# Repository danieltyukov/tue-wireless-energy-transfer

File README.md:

# Wireless Energy Transfer (5XWF0)

Challenge-based learning project for the 5XWF0 Wireless Energy Transfer course at TU
Eindhoven, Q4 2024, built by a team of nine. The goal was to wirelessly power a desktop PC
from a sustainable energy source across an air gap of 10 to 20 cm, delivering at least
100 W and tracking the maximum power point. The full chain is a generator (energy source),
a DC/DC boost converter that stabilizes the variable input to 50 V, a full-bridge DC/AC
inverter, a pair of resonant magnetically coupled coils, an AC/DC rectifier, and the load,
all coordinated by a microcontroller that measures voltages and currents and sets the PWM
duty cycle and switching frequency.

My part of the project was the DC/DC boost converter: the topology and component choices,
a MATLAB script for selecting the inductor and capacitor values, the KiCad PCB, and the
hardware testing. The sections and appendices for that subsystem in the final report are
mine (design choices, testing, and the component-selection script).

## The DC/DC boost converter

The converter takes the generator's variable rectified DC (up to 30 V, limited to 10 A)
and boosts it to a regulated 50 V for the rest of the chain. Design decisions and their
reasoning:

- **Topology.** A standard boost converter, chosen over buck-boost and Cuk alternatives.
  Those give a wider input range but add an inverted output, a negative gate-drive supply,
  or a second inductor, all of which raise complexity and losses.
- **Passives.** A 75 to 125 uH inductor sized to keep the converter in continuous
  conduction mode with margin, and a 220 uF output capacitor. In simulation this holds the
  output at about 49 V with 4.95 % ripple, inside the 5 % requirement. The minimum values
  were computed with a MATLAB script that sweeps the input voltage range (`Appendix D` of
  the report).
- **Switches and diode.** An IRF640 power MOSFET, picked over the IRF630 because its lower
  on-resistance cuts conduction losses more than the added switching loss costs, and an
  MBR10100+ Schottky diode rated for the worst-case current at low duty cycle.
- **Switching frequency.** 20 kHz, a tradeoff that keeps switching losses low while still
  meeting the ripple targets without an oversized inductor.
- **Control.** A low-side gate driver so the microcontroller can drive the duty cycle
  directly, with the duty cycle held near 0.5 and constrained to keep the input current
  under the 10 A generator limit.

The board was laid out in KiCad with a continuous ground plane, current-scaled trace
widths, and component placement chosen to spread heat and limit EMI.

Testing started at low voltage and current on the PCB, cross-checked against the
breadboard build to isolate faults (a diode footprint mismatch, misplaced input
capacitors, and wrong voltage-divider resistor values were found and fixed), then ramped
up to 150 W.

## Result

The integrated system reached a tested peak efficiency of 77.36 % at 180.80 W output,
passing the 100 W minimum. The power electronics PCBs worked as designed. MPPT and
automatic load detection were designed but not fully brought up in hardware within the
project time, and the report documents the gap between the MATLAB and Simulink models and
the measured system as the main lesson for future work.

## Repository structure

```
5XWF0_Final_Report.pdf      full team report (design, models, testing, results)
dc-to-dc-maker/             DC/DC boost converter: KiCad project, gerbers, part libraries
dc-to-ac-maker/             DC/AC full-bridge inverter KiCad project
CODING/                     microcontroller firmware (STM32 F303K8 and ESP32), PWM/ADC/MPPT
STM32 - F303K8 code/        packaged STM32CubeIDE firmware builds
team-microcontroller/       microcontroller subteam working files
*.slx                       Simulink models of the full system
```

## Building and running

The converter and inverter boards open in KiCad (`.kicad_pro` / `.kicad_pcb` /
`.kicad_sch`), with gerbers included for fabrication. The firmware under
`CODING/Final Codes/C-Code` is STM32CubeIDE C for the Nucleo F303K8 (PWM plus ADC
variants, including an MPPT-via-ADC version). The `.slx` files are Simulink models of the
full transfer chain and are opened in MATLAB/Simulink.

## Technologies

KiCad (PCB design and gerbers), power electronics (boost converter, full-bridge inverter,
resonant inductive coupling), MATLAB and Simulink, STM32 (Nucleo F303K8, STM32CubeIDE, C)
and ESP32 firmware, and bench testing with an oscilloscope and impedance analyzer.

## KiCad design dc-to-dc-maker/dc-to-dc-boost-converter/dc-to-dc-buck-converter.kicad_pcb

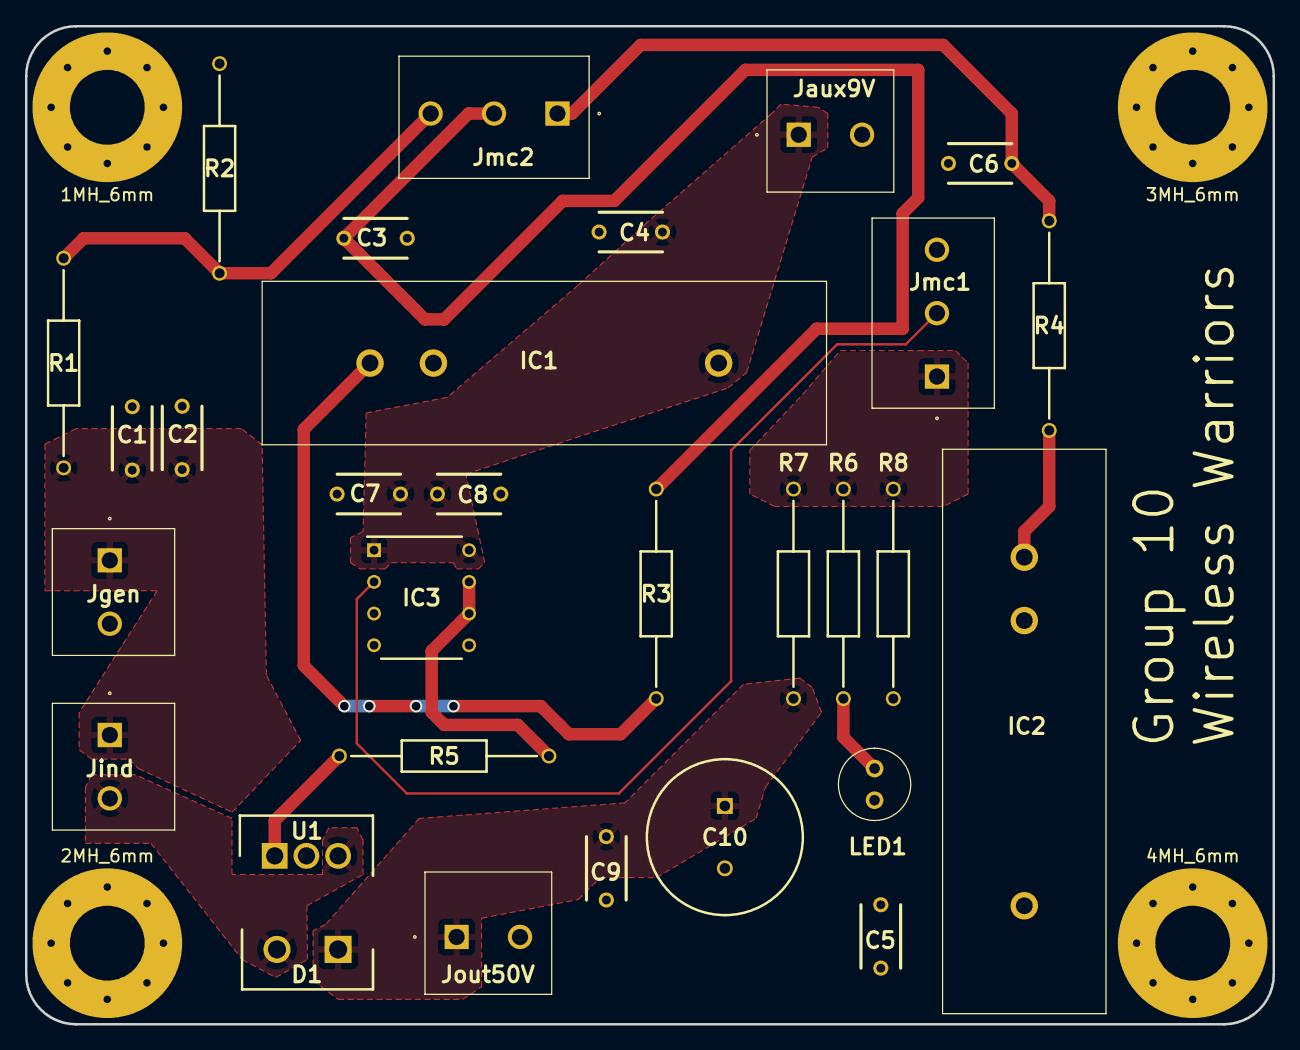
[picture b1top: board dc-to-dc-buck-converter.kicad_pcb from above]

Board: 2 copper layers, 100.0 x 80.0 mm, 34 parts (0 on the bottom side), 15 nets.

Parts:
1MH_6mm, 2MH_6mm, 3MH_6mm, 4MH_6mm: MH_6mm; MountingHole_6mm_Pad_Via
C1, C2, C3, C4, C5, C6, C7, C8, C9: 0.1uF; C322
C10: 220uF; CAPPRD500W65D1250H2200
D1: MBR10100+; TO490P480X1000X2110-2P
IC1, IC2: LA_55-P; LA55-P
IC3: EL7104CNZ; DIP762W51P254L952H533Q8N
Jaux9V: Jaux; 1715721
Jgen: Jgen; 1715721
Jind: Jind; 1715721
Jmc1, Jmc2: 1715734
Jout50V: Jout +50V; 1715721
LED1: TLUR5400
R1, R7: 20K; RESAD1680W59L680D250
R2, R8: 1K; RESAD1680W59L680D250
R3, R4: 100; RESAD1680W59L680D250
R5, R6: 10; RESAD1680W59L680D250
U1: IRF640NPBF; TO254P483X1016X1994-3P

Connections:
GND: C1.1, C2.1, C3.2, C4.2, C5.2, C6.2, C7.1, C8.1, C9.1, C10.2 (-), IC1.2 (NEG), IC2.2 (NEG), IC3.4 (GND_1), IC3.5 (GND_2), Jaux9V.2, Jgen.2, Jmc1.3, Jout50V.2, LED1.2 (K), R2.1, R8.1, U1.2 (SOURCE)
unnamed: C1.2, C2.2, Jgen.1, Jind.1, R1.2
unnamed: C3.1, Jmc2.2, R3.1
unnamed: C6.1, Jmc2.1, R4.1
unnamed: C9.2, C10.1 (+), D1.1 (K), Jout50V.1, R7.2
unnamed: D1.2 (A), Jind.2, U1.3 (DRAIN)
unnamed: IC1.1 (M), R3.2
unnamed: C4.1, C5.1, C7.2, C8.2, IC1.3 (POS), IC2.3 (POS), IC3.1 (V+_1), IC3.8 (V+_2), Jaux9V.1
unnamed: IC2.1 (M), R4.2
unnamed: IC3.2 (IN), Jmc1.2
unnamed: IC3.6 (N_OUT), IC3.7 (P_OUT), R5.1
unnamed: Jmc1.1, R6.1, R7.1, R8.2
unnamed: Jmc2.3, R1.1, R2.2
unnamed: LED1.1 (A), R6.2
unnamed: R5.2, U1.1 (GATE)

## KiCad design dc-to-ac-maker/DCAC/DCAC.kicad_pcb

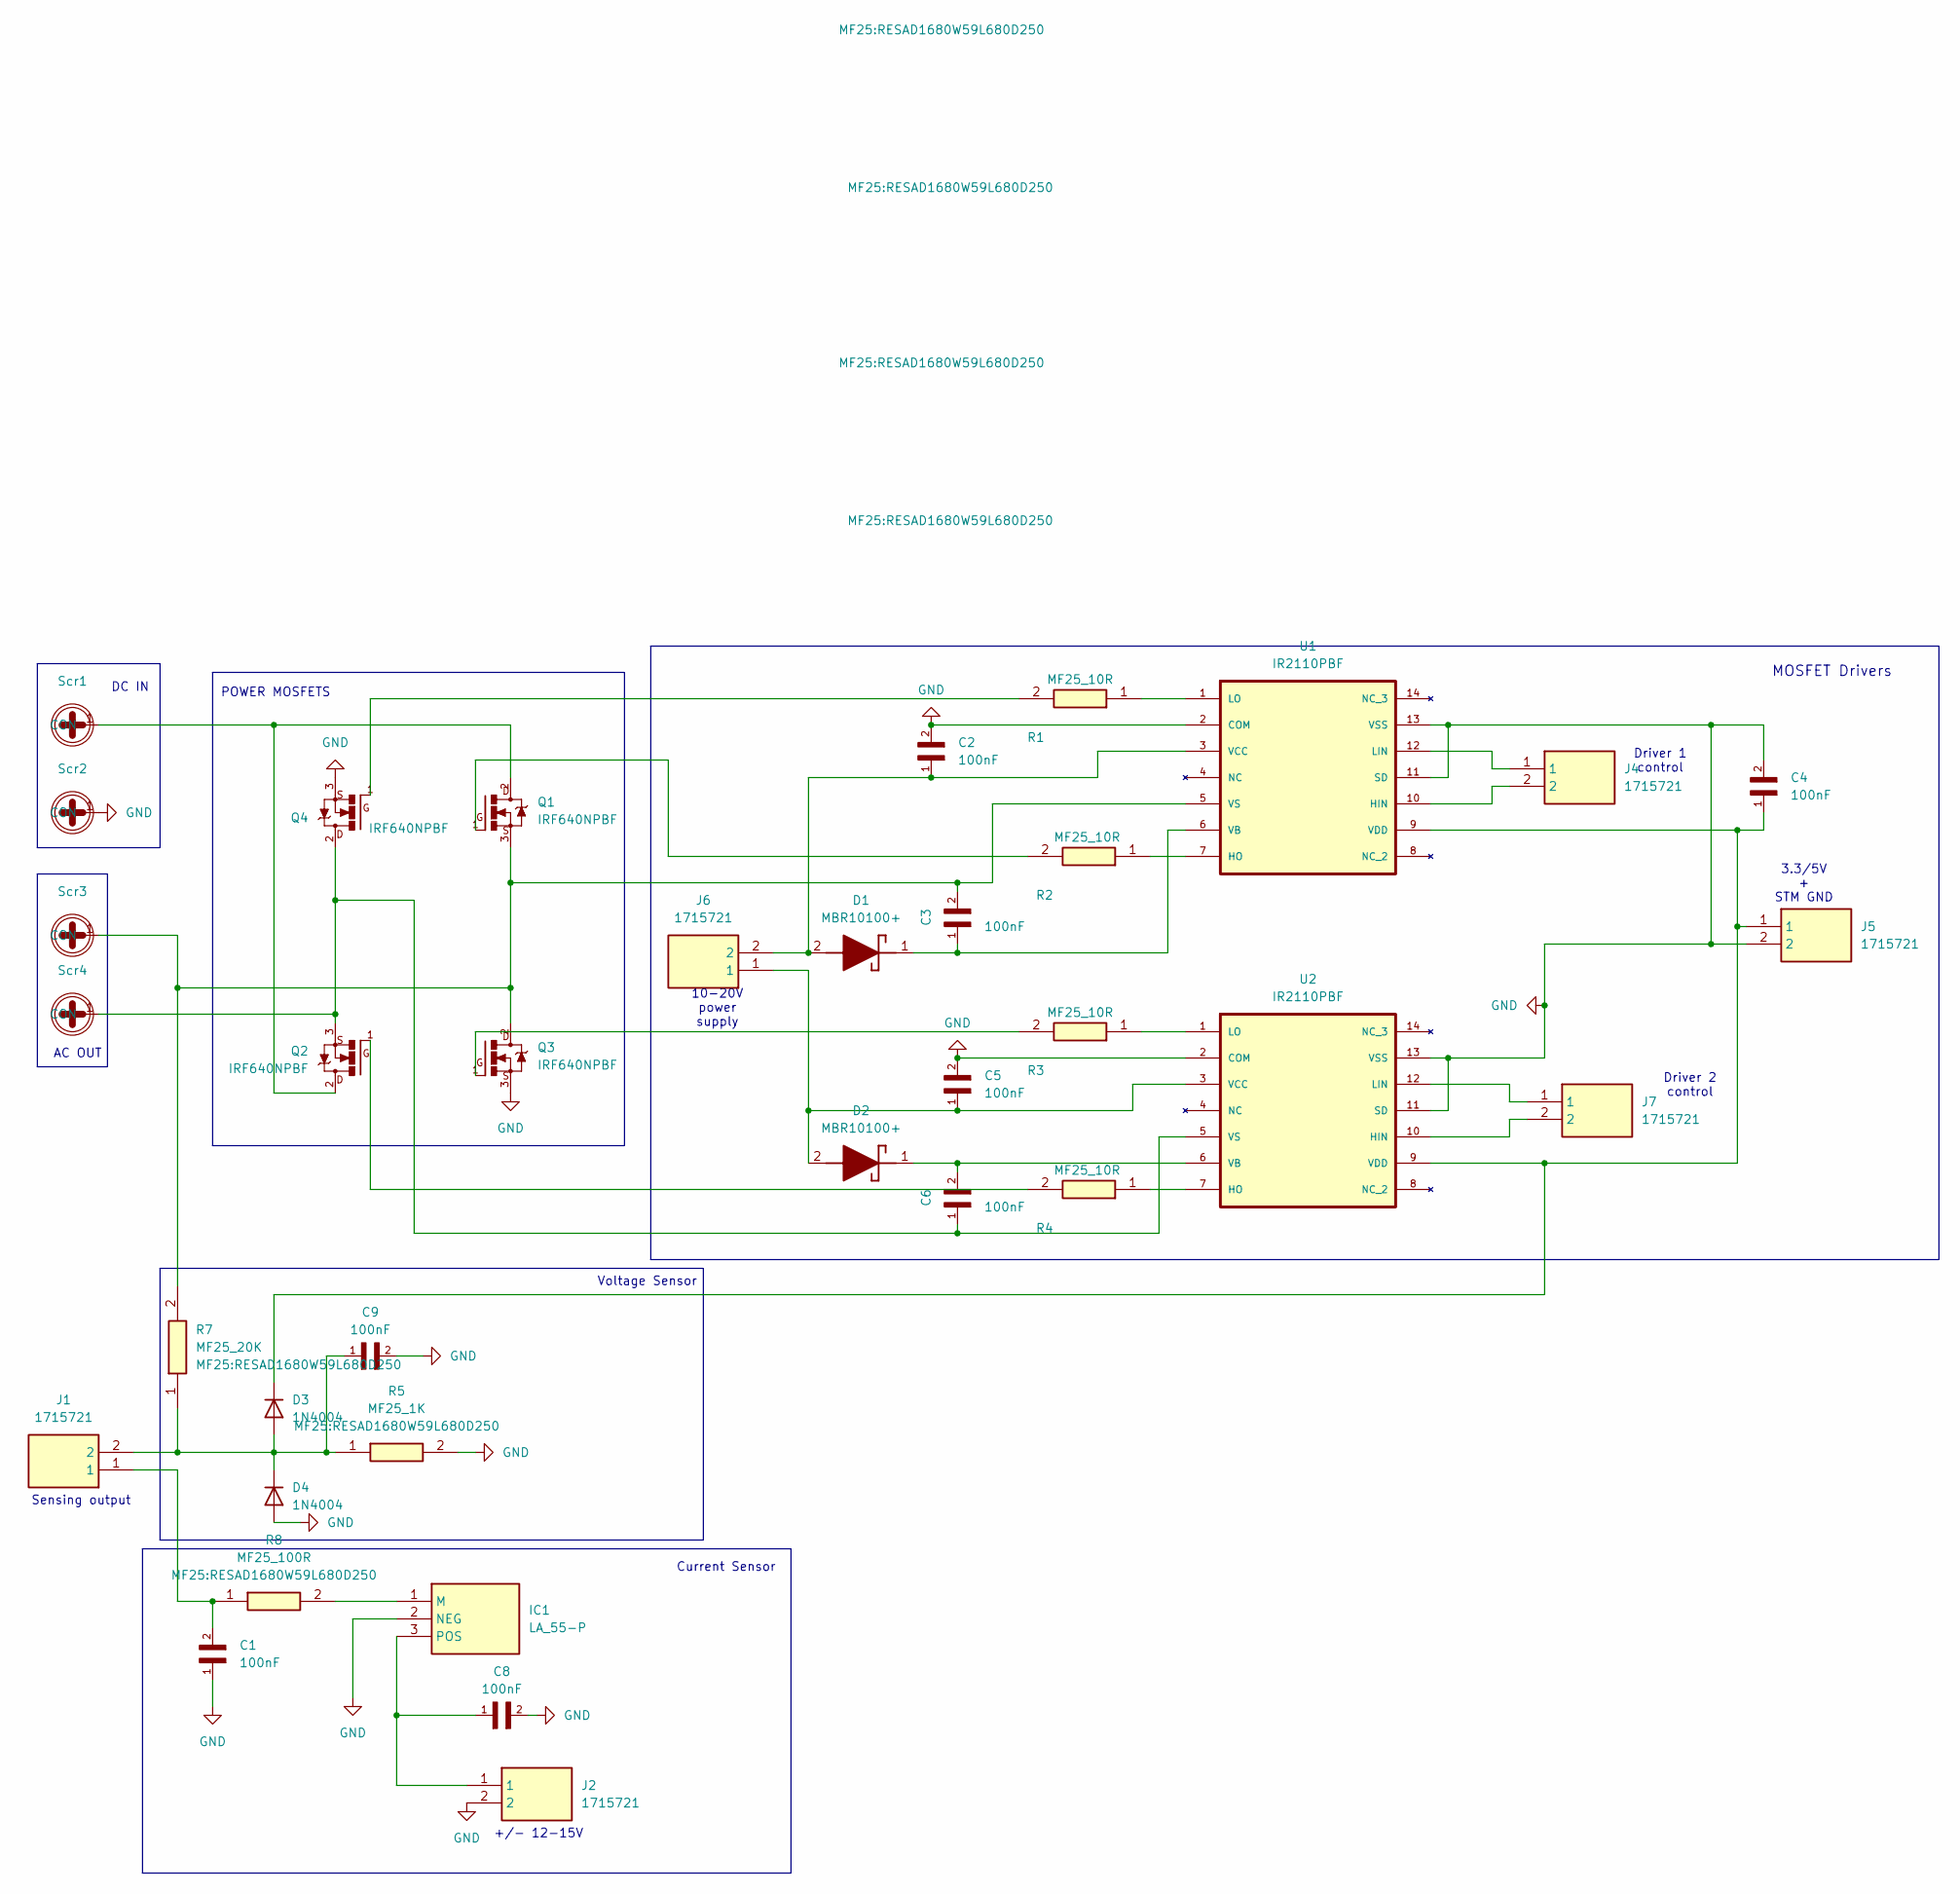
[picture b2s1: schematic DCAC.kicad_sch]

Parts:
C1, C2, C3, C4, C5, C6, C8, C9: 100nF; CAPRR500W50L730T250H650; PARTREV 2020-06
D1, D2: MBR10100+; TO490P480X1000X2110-2P; Manufacturer_Part_Number MBR10100+
D3, D4: 1N4004; D_DO-41_SOD81_P10.16mm_Horizontal
IC1: LA_55-P; LA55-P; Manufacturer_Part_Number LA 55-P
J1, J2, J4, J5, J6, J7: 1715721; PARTREV 27.04.2017; Mouser Part Number 651-1715721
Q1, Q2, Q3, Q4: IRF640NPBF; TO220V
R1, R2, R3, R4: MF25_10R; RESAD1680W59L680D250; Manufacturer_Part_Number MF25 10R
R5: MF25_1K; RESAD1680W59L680D250; Manufacturer_Part_Number MF25 10R
R7: MF25_20K; RESAD1680W59L680D250; Manufacturer_Part_Number MF25 10R
R8: MF25_100R; RESAD1680W59L680D250; Manufacturer_Part_Number MF25 10R
Scr1, Scr2, Scr3, Scr4: MountingHole_6.4mm_M6_Pad_Via
U1, U2: IR2110PBF; DIP254P762X533-14; MPN IR2110PBF

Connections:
GND: C1.1, C2.2, C4.2, C5.2, C8.2, C9.2, D4.2 (A), IC1.2 (NEG), J2.2, J5.2, Q3.3, Q4.3, R5.2, Scr2.1 (CON), U1.2 (COM), U1.11 (SD), U1.13 (VSS), U2.2 (COM), U2.11 (SD), U2.13 (VSS)
unnamed: C1.2, J1.1, R8.1
unnamed: C2.1, D1.2 (A), J6.2, U1.3 (VCC)
unnamed: C3.1, D1.1 (K), U1.6 (VB)
unnamed: C5.1, D2.2 (A), J6.1, U2.3 (VCC)
unnamed: C6.2, D2.1 (K), U2.6 (VB)
unnamed: C9.1, D3.2 (A), D4.1 (K), J1.2, R5.1, R7.1
unnamed: C4.1, D3.1 (K), J5.1, U1.9 (VDD), U2.9 (VDD)
unnamed: IC1.1 (M), R8.2
unnamed: C8.1, IC1.3 (POS), J2.1
unnamed: Q1.1, R2.2
unnamed: Q2.1, R4.2
unnamed: Q3.1, R3.2
unnamed: Q4.1, R1.2
unnamed: Q1.2, Q2.2, Scr1.1 (CON)
unnamed: C3.2, Q1.3, Q3.2, R7.2, Scr3.1 (CON), U1.5 (VS)
unnamed: C6.1, Q2.3, Q4.2, Scr4.1 (CON), U2.5 (VS)
unnamed: J4.2, U1.10 (HIN)
unnamed: R2.1, U1.7 (HO)
unnamed: J4.1, U1.12 (LIN)
unnamed: R1.1, U1.1 (LO)
unnamed: J7.2, U2.10 (HIN)
unnamed: R4.1, U2.7 (HO)
unnamed: J7.1, U2.12 (LIN)
unnamed: R3.1, U2.1 (LO)

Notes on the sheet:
Sensing output
POWER MOSFETS
AC OUT
+/- 12-15V
Driver 1 control
MOSFET Drivers
3.3/5V + STM GND
Current Sensor
Driver 2 control
DC IN
10-20V power supply
Voltage Sensor

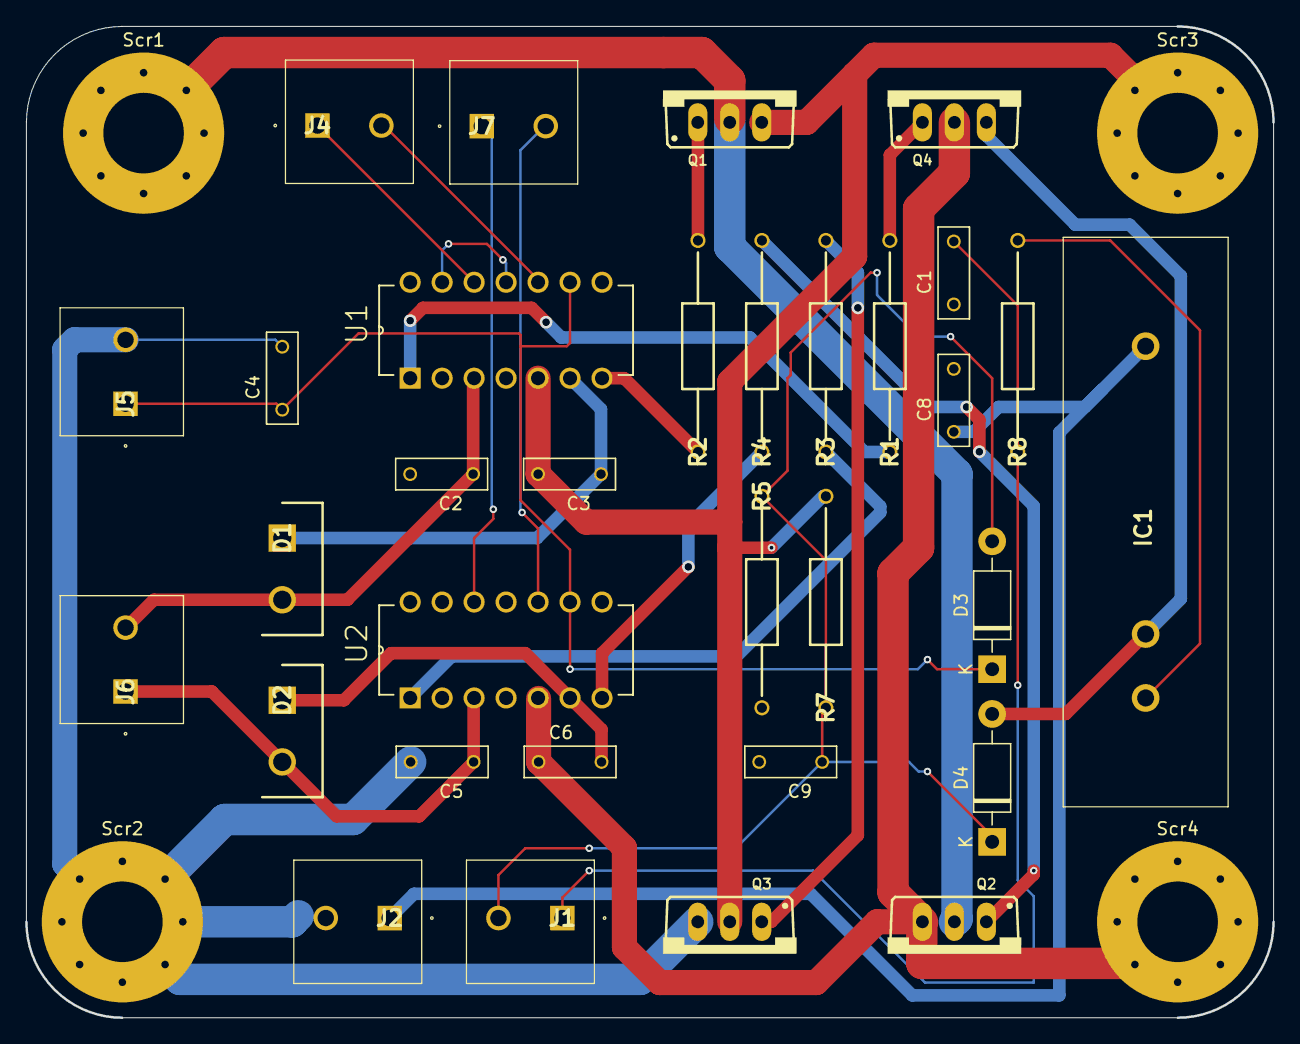
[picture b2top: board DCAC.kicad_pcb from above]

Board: 2 copper layers, 99.1 x 78.7 mm, 36 parts (0 on the bottom side), 25 nets.

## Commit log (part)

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2024-04-22 first
2024-04-22 initial setup
2024-04-22 removed temp
2024-04-27 moved to stm32cube
2024-05-05 Create Power Electronics file
2024-05-06 Create DC-DC buckboost wrong Vout
2024-05-08 Ben's code
    Commit to private branch
2024-05-12 update to backups
2024-05-12 algorithm
2024-05-12 Rename 5XWF0.ino to 5XWF0-Algorithm.ino
2024-05-12 dc-to-dc circuit kicad
2024-05-15 Create magnetics
2024-05-15 dc to dc
2024-05-15 update name
2024-05-16 pcb structure + images
2024-05-18 update to pcb placement
2024-05-19 pcb final
2024-05-28 Create y
2024-05-30 Create info
2024-06-17 Create X
2024-07-30 added final report
2024-07-30 added final coding stuff
